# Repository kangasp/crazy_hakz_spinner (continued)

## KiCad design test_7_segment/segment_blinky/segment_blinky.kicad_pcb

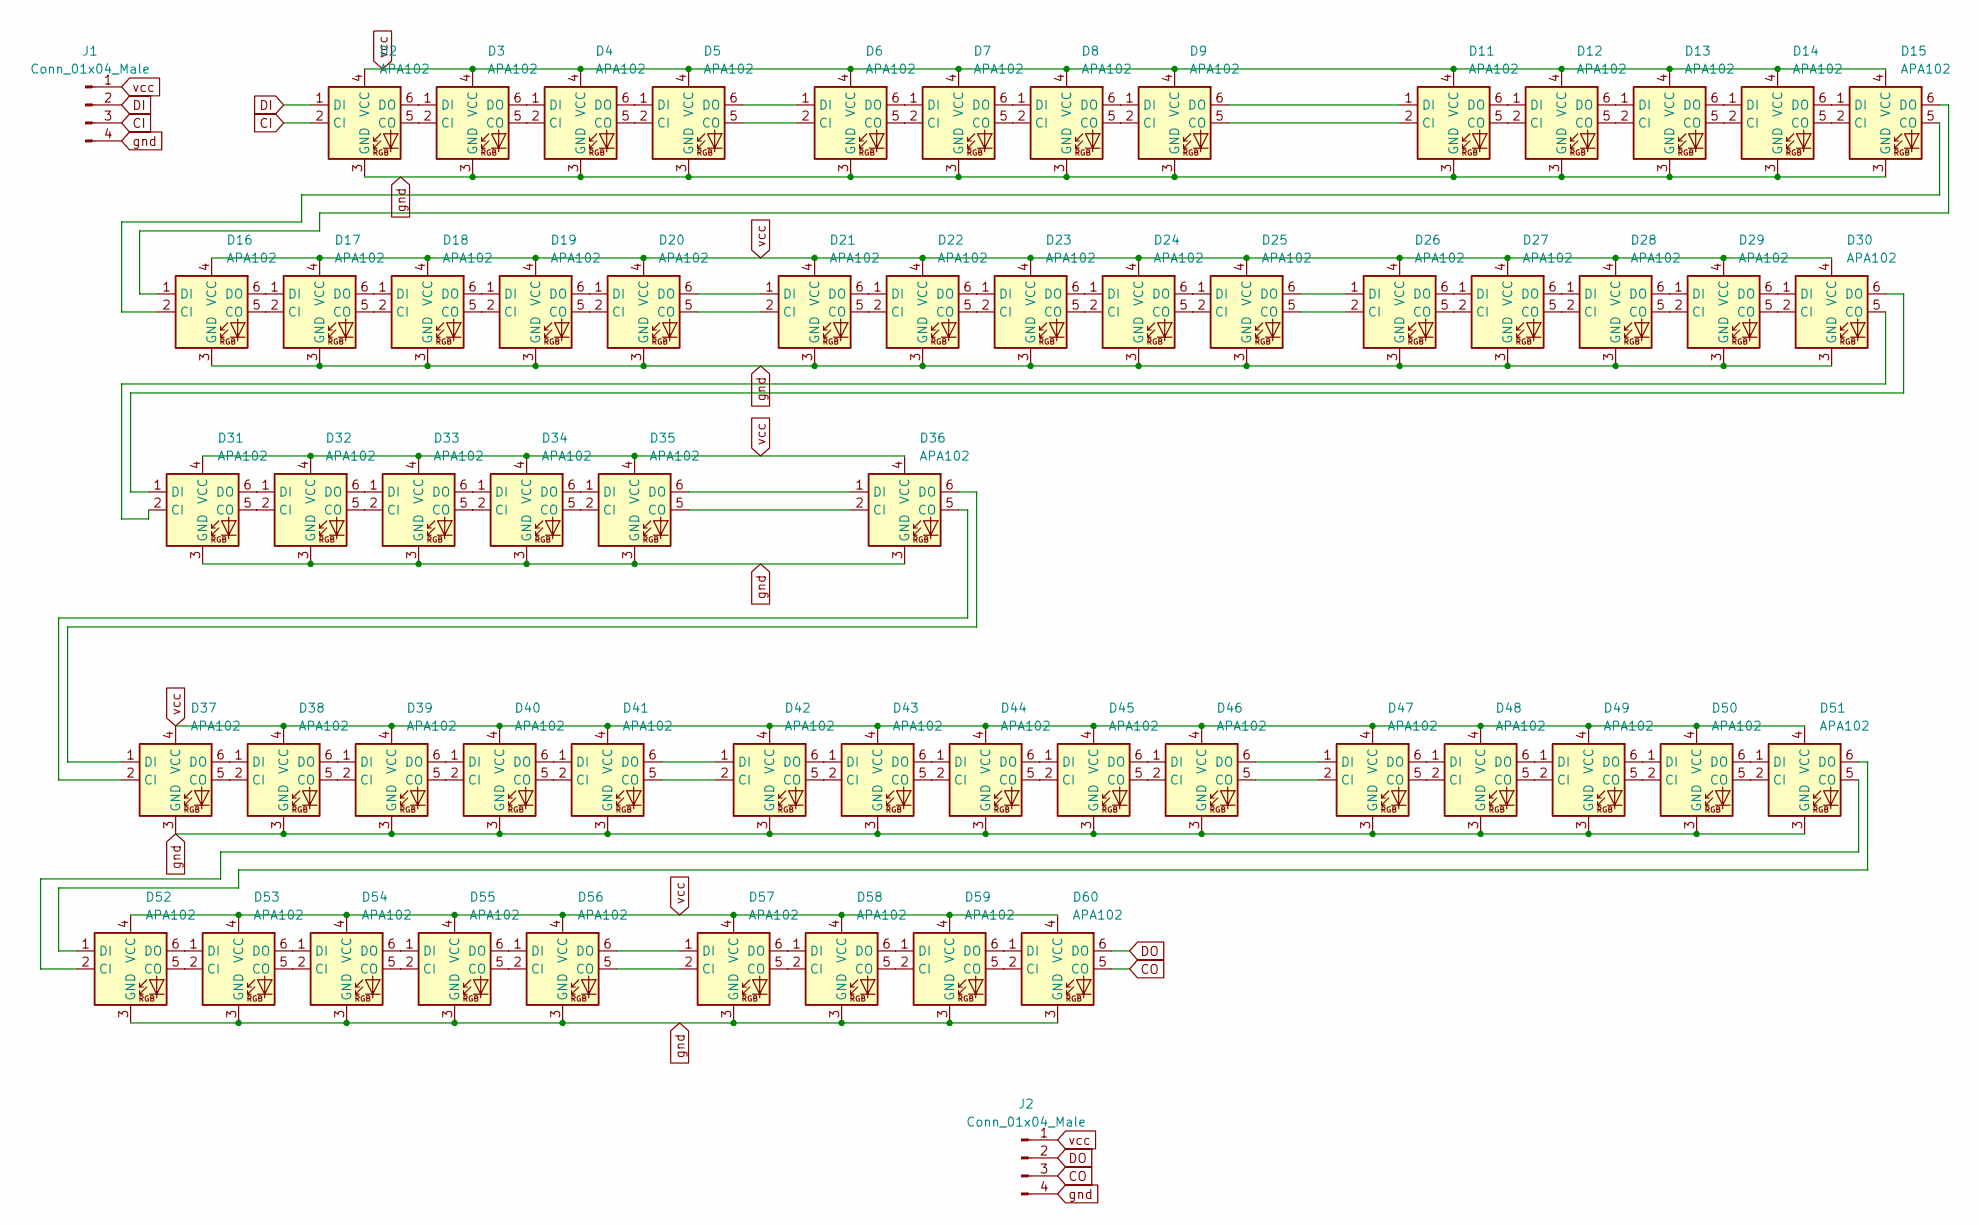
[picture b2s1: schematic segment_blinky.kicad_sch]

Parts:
D2, D3, D4, D5, D6, D7, D8, D9, D11, D12, D13, D14, D15, D16, D17, D18, D19, D20, D21, D22, D23, D24, D25, D26, D27, D28, D29, D30, D31, D32, D33, D34, D35, D36, D37, D38, D39, D40, D41, D42, D43, D44, D45, D46, D47, D48, D49, D50, D51, D52, D53, D54, D55, D56, D57, D58, D59, D60: APA102; SK9822-hakz
J1, J2: Conn_01x04_Male; PinHeader_1x04_P2.54mm_Vertical

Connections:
CI: D2.2 (CI), J1.3
CO: D60.5 (CO), J2.3
DI: D2.1 (DI), J1.2
DO: D60.6 (DO), J2.2
unnamed: D2.5 (CO), D3.2 (CI)
unnamed: D2.6 (DO), D3.1 (DI)
unnamed: D3.5 (CO), D4.2 (CI)
unnamed: D3.6 (DO), D4.1 (DI)
unnamed: D4.5 (CO), D5.2 (CI)
unnamed: D4.6 (DO), D5.1 (DI)
unnamed: D5.5 (CO), D6.2 (CI)
unnamed: D5.6 (DO), D6.1 (DI)
unnamed: D6.5 (CO), D7.2 (CI)
unnamed: D6.6 (DO), D7.1 (DI)
unnamed: D7.5 (CO), D8.2 (CI)
unnamed: D7.6 (DO), D8.1 (DI)
unnamed: D8.5 (CO), D9.2 (CI)
unnamed: D8.6 (DO), D9.1 (DI)
unnamed: D9.5 (CO), D11.2 (CI)
unnamed: D9.6 (DO), D11.1 (DI)
unnamed: D11.5 (CO), D12.2 (CI)
unnamed: D11.6 (DO), D12.1 (DI)
unnamed: D12.5 (CO), D13.2 (CI)
unnamed: D12.6 (DO), D13.1 (DI)
unnamed: D13.5 (CO), D14.2 (CI)
unnamed: D13.6 (DO), D14.1 (DI)
unnamed: D14.5 (CO), D15.2 (CI)
unnamed: D14.6 (DO), D15.1 (DI)
unnamed: D15.5 (CO), D16.2 (CI)
unnamed: D15.6 (DO), D16.1 (DI)
unnamed: D16.5 (CO), D17.2 (CI)
unnamed: D16.6 (DO), D17.1 (DI)
unnamed: D17.5 (CO), D18.2 (CI)
unnamed: D17.6 (DO), D18.1 (DI)
unnamed: D18.5 (CO), D19.2 (CI)
unnamed: D18.6 (DO), D19.1 (DI)
unnamed: D19.5 (CO), D20.2 (CI)
unnamed: D19.6 (DO), D20.1 (DI)
unnamed: D20.5 (CO), D21.2 (CI)
unnamed: D20.6 (DO), D21.1 (DI)
unnamed: D21.5 (CO), D22.2 (CI)
unnamed: D21.6 (DO), D22.1 (DI)
unnamed: D22.5 (CO), D23.2 (CI)
unnamed: D22.6 (DO), D23.1 (DI)
unnamed: D23.5 (CO), D24.2 (CI)
unnamed: D23.6 (DO), D24.1 (DI)
unnamed: D24.5 (CO), D25.2 (CI)
unnamed: D24.6 (DO), D25.1 (DI)
unnamed: D25.5 (CO), D26.2 (CI)
unnamed: D25.6 (DO), D26.1 (DI)
unnamed: D26.5 (CO), D27.2 (CI)
unnamed: D26.6 (DO), D27.1 (DI)
unnamed: D27.5 (CO), D28.2 (CI)
unnamed: D27.6 (DO), D28.1 (DI)
unnamed: D28.5 (CO), D29.2 (CI)
unnamed: D28.6 (DO), D29.1 (DI)
unnamed: D29.5 (CO), D30.2 (CI)
unnamed: D29.6 (DO), D30.1 (DI)
unnamed: D30.5 (CO), D31.2 (CI)
unnamed: D30.6 (DO), D31.1 (DI)
unnamed: D31.5 (CO), D32.2 (CI)
unnamed: D31.6 (DO), D32.1 (DI)
unnamed: D32.5 (CO), D33.2 (CI)
unnamed: D32.6 (DO), D33.1 (DI)
unnamed: D33.5 (CO), D34.2 (CI)
unnamed: D33.6 (DO), D34.1 (DI)
unnamed: D34.5 (CO), D35.2 (CI)
unnamed: D34.6 (DO), D35.1 (DI)
unnamed: D35.5 (CO), D36.2 (CI)
unnamed: D35.6 (DO), D36.1 (DI)
unnamed: D36.5 (CO), D37.2 (CI)
unnamed: D36.6 (DO), D37.1 (DI)
unnamed: D37.5 (CO), D38.2 (CI)
unnamed: D37.6 (DO), D38.1 (DI)
unnamed: D38.5 (CO), D39.2 (CI)
unnamed: D38.6 (DO), D39.1 (DI)
unnamed: D39.5 (CO), D40.2 (CI)
unnamed: D39.6 (DO), D40.1 (DI)
unnamed: D40.5 (CO), D41.2 (CI)
unnamed: D40.6 (DO), D41.1 (DI)
unnamed: D41.5 (CO), D42.2 (CI)
unnamed: D41.6 (DO), D42.1 (DI)
unnamed: D42.5 (CO), D43.2 (CI)
unnamed: D42.6 (DO), D43.1 (DI)
unnamed: D43.5 (CO), D44.2 (CI)
unnamed: D43.6 (DO), D44.1 (DI)
unnamed: D44.5 (CO), D45.2 (CI)
unnamed: D44.6 (DO), D45.1 (DI)
unnamed: D45.5 (CO), D46.2 (CI)
unnamed: D45.6 (DO), D46.1 (DI)
unnamed: D46.5 (CO), D47.2 (CI)
unnamed: D46.6 (DO), D47.1 (DI)
unnamed: D47.5 (CO), D48.2 (CI)
unnamed: D47.6 (DO), D48.1 (DI)
unnamed: D48.5 (CO), D49.2 (CI)
unnamed: D48.6 (DO), D49.1 (DI)
unnamed: D49.5 (CO), D50.2 (CI)
unnamed: D49.6 (DO), D50.1 (DI)
unnamed: D50.5 (CO), D51.2 (CI)
unnamed: D50.6 (DO), D51.1 (DI)
unnamed: D51.5 (CO), D52.2 (CI)
unnamed: D51.6 (DO), D52.1 (DI)
unnamed: D52.5 (CO), D53.2 (CI)
unnamed: D52.6 (DO), D53.1 (DI)
unnamed: D53.5 (CO), D54.2 (CI)
unnamed: D53.6 (DO), D54.1 (DI)
unnamed: D54.5 (CO), D55.2 (CI)
unnamed: D54.6 (DO), D55.1 (DI)
unnamed: D55.5 (CO), D56.2 (CI)
unnamed: D55.6 (DO), D56.1 (DI)
unnamed: D56.5 (CO), D57.2 (CI)
unnamed: D56.6 (DO), D57.1 (DI)
unnamed: D57.5 (CO), D58.2 (CI)
unnamed: D57.6 (DO), D58.1 (DI)
unnamed: D58.5 (CO), D59.2 (CI)
unnamed: D58.6 (DO), D59.1 (DI)
unnamed: D59.5 (CO), D60.2 (CI)
unnamed: D59.6 (DO), D60.1 (DI)
gnd: D2.3 (GND), D3.3 (GND), D4.3 (GND), D5.3 (GND), D6.3 (GND), D7.3 (GND), D8.3 (GND), D9.3 (GND), D11.3 (GND), D12.3 (GND), D13.3 (GND), D14.3 (GND), D15.3 (GND), D16.3 (GND), D17.3 (GND), D18.3 (GND), D19.3 (GND), D20.3 (GND), D21.3 (GND), D22.3 (GND), D23.3 (GND), D24.3 (GND), D25.3 (GND), D26.3 (GND), D27.3 (GND), D28.3 (GND), D29.3 (GND), D30.3 (GND), D31.3 (GND), D32.3 (GND), D33.3 (GND), D34.3 (GND), D35.3 (GND), D36.3 (GND), D37.3 (GND), D38.3 (GND), D39.3 (GND), D40.3 (GND), D41.3 (GND), D42.3 (GND), D43.3 (GND), D44.3 (GND), D45.3 (GND), D46.3 (GND), D47.3 (GND), D48.3 (GND), D49.3 (GND), D50.3 (GND), D51.3 (GND), D52.3 (GND), D53.3 (GND), D54.3 (GND), D55.3 (GND), D56.3 (GND), D57.3 (GND), D58.3 (GND), D59.3 (GND), D60.3 (GND), J1.4, J2.4
vcc: D2.4 (VCC), D3.4 (VCC), D4.4 (VCC), D5.4 (VCC), D6.4 (VCC), D7.4 (VCC), D8.4 (VCC), D9.4 (VCC), D11.4 (VCC), D12.4 (VCC), D13.4 (VCC), D14.4 (VCC), D15.4 (VCC), D16.4 (VCC), D17.4 (VCC), D18.4 (VCC), D19.4 (VCC), D20.4 (VCC), D21.4 (VCC), D22.4 (VCC), D23.4 (VCC), D24.4 (VCC), D25.4 (VCC), D26.4 (VCC), D27.4 (VCC), D28.4 (VCC), D29.4 (VCC), D30.4 (VCC), D31.4 (VCC), D32.4 (VCC), D33.4 (VCC), D34.4 (VCC), D35.4 (VCC), D36.4 (VCC), D37.4 (VCC), D38.4 (VCC), D39.4 (VCC), D40.4 (VCC), D41.4 (VCC), D42.4 (VCC), D43.4 (VCC), D44.4 (VCC), D45.4 (VCC), D46.4 (VCC), D47.4 (VCC), D48.4 (VCC), D49.4 (VCC), D50.4 (VCC), D51.4 (VCC), D52.4 (VCC), D53.4 (VCC), D54.4 (VCC), D55.4 (VCC), D56.4 (VCC), D57.4 (VCC), D58.4 (VCC), D59.4 (VCC), D60.4 (VCC), J1.1, J2.1

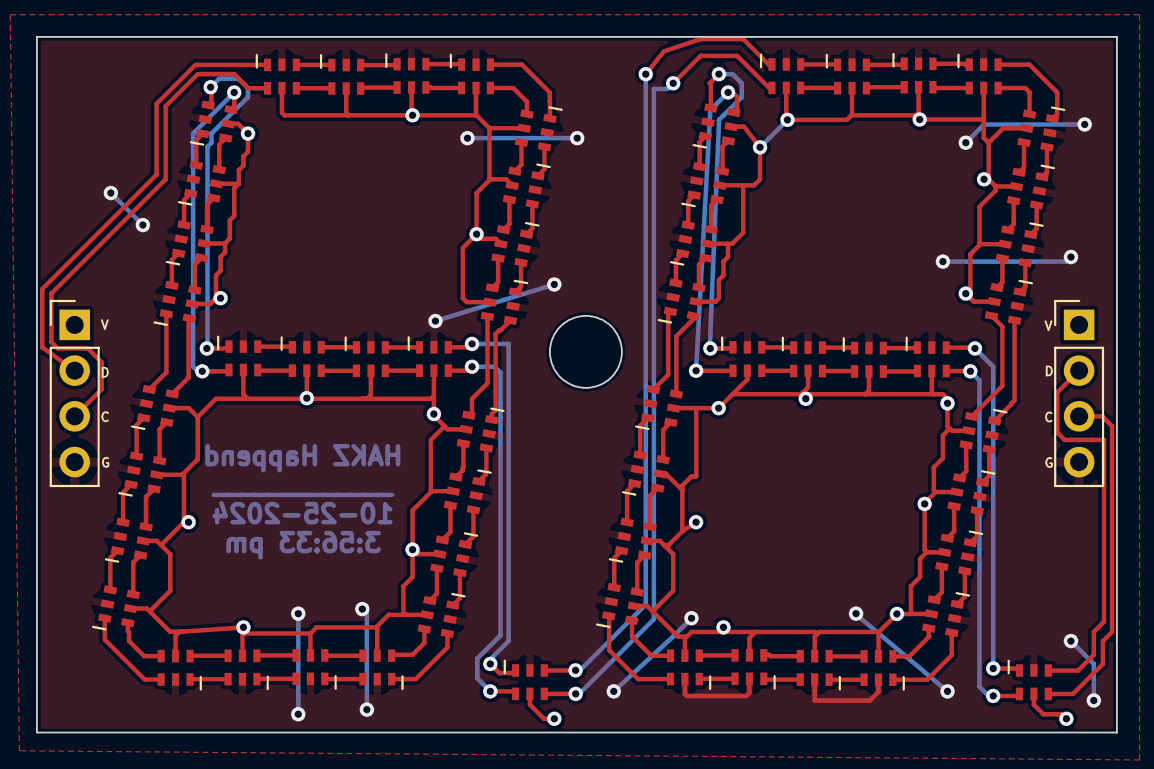
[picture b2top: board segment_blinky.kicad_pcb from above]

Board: 2 copper layers, 60.0 x 38.6 mm, 60 parts (0 on the bottom side), 120 nets.

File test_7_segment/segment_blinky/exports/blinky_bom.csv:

"Comment","Designator","Footprint","JLCPCDB Part #"
"LED","D7,D6,D42,D36,D24,D14,D26,D50,D8,D15,D59,D22,D55,D39,D44,D48,D9,D46,D11,D4,D49,D38,D53,D54,D21,D56,D17,D28,D45,D43,D47,D27,D60,D57,D30,D31,D35,D34,D32,D58,D37,D12,D2,D33,D51,D19,D29,D52,D13,D5,D41,D23,D18,D25,D16,D40,D20,D3","SK9822-hakz","C2909059"

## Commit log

2022-11-19 IDK. Add the kitchen sink.
2022-11-19 Adding all the things.
2022-11-23 Add a initial plugin for rounding things.
2022-12-16 Update things. Next checkin.
2022-12-30 Adding all kinds of things.
2023-01-07 Adding the BOM and more backups and updates to kicad files.
2023-01-17 Update schematice, etc, etc.
2023-02-03 Add code that may or may not work, for LEDs!!
2023-02-25 Add notes from meeting. Things to update.
2023-03-24 IDK.
2023-03-24 Updated schematic and things. For spin 2. And board layout.
2023-03-31 Adding the rod_bracket that holds the spinner to spin.
2023-03-31 Add STL folder, add crown and rod bracket.
2023-04-25 Add crown with supports.
2023-08-18 Adding things: SD card, resistor pack, routing. Totally done.
    Issue: HKZ-563
    Changelog: No Functional Change.
2023-08-25 Adding the FINAL version (final_01_A_REAL_FINAL). V2
2024-01-13 inital Fibo,
2024-01-30 SPI turns on the lights.
2024-02-02 Make the lEDs go in color.
2024-02-04 Adding a rotary encoder lib.
2024-02-04 Revert "Adding a rotary encoder lib."
    This is hitting an assert on the interrupt.
    Docs say its for idf 3.3, I'm using 4.4
    This reverts commit 7da6d3bf328103cd7d3aabb0c6c265cfe1c53036.
2024-02-04 Using 4.4 version of PCNT rotary encoder.
2024-02-10 Did some things. Without the print, it looked like it workt.
2024-02-23 Added gui tool for images.
2024-02-23 Added binaries
2024-02-23 Added built binaries
2024-02-23 Fixed 360 build
2024-02-23 Changed output to uint8.
2024-02-23 Trying to pull in the new formatted image.
2024-02-23 IDK... triangle pattern... 24 of them.
2024-02-23 This works.
2024-02-23 Closer but borkn.
2024-03-01 WORKT!! Remove the janky buf shifting madness.
2024-03-08 Updated arc test tool with new features. Removed folders with spaces and added test images.
2024-03-09 Kirby!!!
2024-03-09 Add some images and break the build.
2024-03-22 IDK... update for posterity.
2024-03-22 Adding bare noes softAP http server.
2024-03-22 Did actual OTA. Stole things off the interwebs and it worked.
2024-03-27 Update pics started.
2024-04-01 Added support for saving binary files for OTA uploading.
2024-04-12 SD card write works!!
2024-04-19 Add ability to read image off card. Also ability to crash.
2024-04-26 Switch files and display every 500 ms.
2024-05-03 Add cools pics.
2024-05-03 Try not to cry gif works!!
2024-05-10 IDK. borken.
2024-05-10 Oh sorrows... this week failed a bit. Can't read index.html
2024-05-24 IDK. Cant read from the other thread.
2024-05-24 Initial JS!!
2024-05-31 This is cool... not JS.. Kirby pics!!
2024-05-31 Try things. Try to build this.
2024-06-07 Seems to work... upload photo and spinnerfy!!
2024-07-19 We can write to the SD card!! But only 8.3 file names, yo!!
2024-08-09 Full stack 10x dev'ing!
2024-08-09 At least 10x. IDK. Serving off the SD card somewhat.
2024-08-22 Make us boot even without an SD card.
2024-08-22 Add a favicon!!
2024-09-27 Added interrupt for zero refletor thing.
    and apparently kicad thing as well.
2024-10-18 Add the SK8922 footprint.
2024-10-18 Committing things for test segment board.
2024-10-25 Add all the tings for the blinky tests & order it!!
2024-12-06 cleanup, add things.
2024-12-07 Start the mini version of the spinner.
2024-12-14 Place little LEDs into 3 rows.
2024-12-14 Place more LEDs. Not quite done.
2025-01-11 Push LEDs around and shrink board.
    Leaning towards using 3 14500 3.7v batteries.
    And figuring out on-board charging.
2025-01-25 Found a couple parts for bom.
    Chose some through beam things,
    ESP32 module.
2025-02-01 Choose BMS & SD card holder.
2025-02-22 Found a new ESP32 part.
2025-03-08 IDK. Adding lib things. Need to update kicad.
2025-03-08 Add some libs. Need to update the S3 footprint.
2025-03-14 Hooked up the BMS and wrote some notes. Gonna be fire!
2025-03-19 Moving all the version 9.0
2025-03-28 Placed battery and test points, cpu, reduced copmlexity by %50 for %80 of pins.
2025-04-11 Layout things.
2025-04-18 IDK. Add LDO n stuff.
    Issue: HAKZ-100
2025-05-09 Add more parts and things. Power stage is done!! Tots works.
2025-05-16 Decided to ditch the bounce beam. Added labels to SD and USB.
    Amazing resitor layout. Ditched resitor network.
2025-05-23 Did the things... and happiness.
    Placed through beam, boost circuit layout, labeled done things.
2025-06-06 Add a datasheet and make a few connections. etc.
2025-07-11 Added a few more pinouts to the CPU.
2025-07-18 More pinout choices, random dart throwing. Will test.
2025-07-23 Add some datasheets.
2025-08-15 Adding notes from SD testing.
2025-08-30 Added touch pads.
2025-09-14 Adding recent work. schematic & layout are done-ish
2025-09-14 IDK. Some routing.
2025-09-14 Some board layout.
2025-09-19 Do some layout things. Hey remember to add footprints.
    Some parts aren't on the layout cause schematic parts
    don't have footprints.
2025-09-27 Added footprint for SMD pin header. and layout things.
2025-10-02 Changed the power plane to 3.3v from 5v.
    Made footprint for battery jumper.
    Did more routing.
2025-10-04 Updating parts and fixing rules and things.
